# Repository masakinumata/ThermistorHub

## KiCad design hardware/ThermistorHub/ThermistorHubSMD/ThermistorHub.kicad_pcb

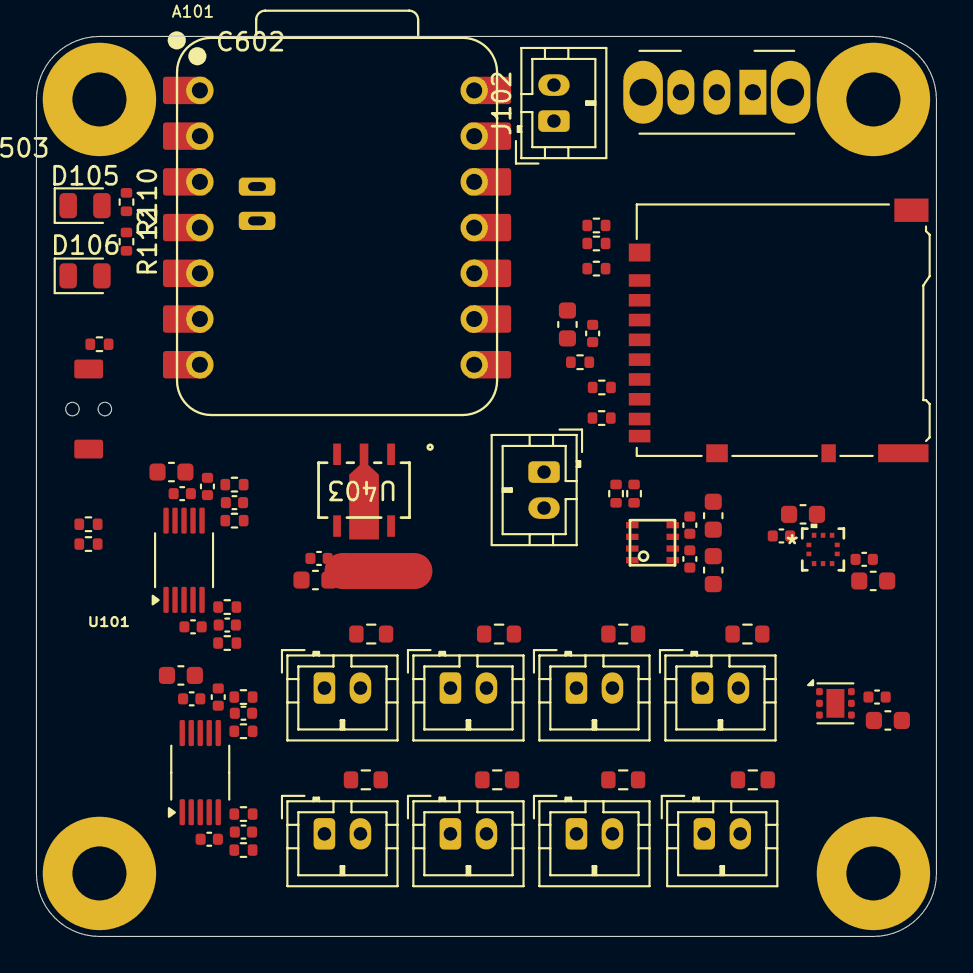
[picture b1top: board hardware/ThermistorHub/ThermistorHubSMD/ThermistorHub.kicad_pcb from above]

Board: 4 copper layers, 50.0 x 50.0 mm, 79 parts (0 on the bottom side), 40 nets, no tracks yet.

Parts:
A101: XIAO-ESP32S3-DIP
B501: Board_1U_60x60
C101, C104, C106, C107, C109, C403, C404, C406, C408: 10μF; C_0603_1608Metric
C102, C103, C105, C108, C110, C401, C402, C405, C407, C501, C502, C503, C504, C601, C602, C603, C604: 100nF; C_0402_1005Metric
D105: STAT; LED_0805_2012Metric
D106: ERROR; LED_0805_2012Metric
J101: BATPin; JST_PH_B2B-PH-K_1x02_P2.00mm_Vertical
J102: Battery; JST_PH_B2B-PH-K_1x02_P2.00mm_Vertical
J301: Micro_SD_Card_Det_Hirose_DM3AT; microSD_HC_Hirose_DM3AT-SF-PEJM5
J501: Thermistor1; JST_PH_B2B-PH-K_1x02_P2.00mm_Vertical
J502: Thermistor2; JST_PH_B2B-PH-K_1x02_P2.00mm_Vertical
J503: Thermistor3; JST_PH_B2B-PH-K_1x02_P2.00mm_Vertical
J504: Thermistor4; JST_PH_B2B-PH-K_1x02_P2.00mm_Vertical
J601: Thermistor5; JST_PH_B2B-PH-K_1x02_P2.00mm_Vertical
J602: Thermistor6; JST_PH_B2B-PH-K_1x02_P2.00mm_Vertical
J603: Thermistor7; JST_PH_B2B-PH-K_1x02_P2.00mm_Vertical
J604: Thermistor8; JST_PH_B2B-PH-K_1x02_P2.00mm_Vertical
NT401: NetTie_2; NetTie-2_SMD_Pad2.0mm
R101, R102, R103, R104, R105, R106, R107, R108, R109, R111: 10k; R_0402_1005Metric
R110, R112, R501, R503, R505, R507, R601, R603, R605, R607: 1k; R_0402_1005Metric
R303: 33Ω; R_0402_1005Metric
R502, R504, R506, R508, R602, R604, R606, R608: 47k; R_0603_1608Metric
SW101: SW_SPDT; SW_Slide_SPDT_Angled_CK_OS102011MA1Q
SW501: SW_Push; TVAF06-A020B-R
U101: BME280
U401, U402: ADS1115IRUGT; VSSOP-10_3x3mm_P0.5mm
U403: NJM2884U1-33-TE1; SOT89-5-1&slash_2_NWJ
U501: BMP390; 10LGA_2X2X0p75_BOS
U502: TMP117xxDRV; WSON-6-1EP_2x2mm_P0.65mm_EP1x1.6mm

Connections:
+3V0: C401.1, C402.1, C403.1, C404.1, C405.1, C406.1, C407.1, C408.1, J501.1, J502.1, J503.1, J504.1, J601.1, J602.1, J603.1, J604.1, R108.1, R109.1, U401.8 (VDD), U402.1 (ADDR), U402.8 (VDD), U403.4 (VOUT), U502.5 (V+)
/CLK: A101.11 (GPIO9), R303.1
/CMD: A101.10 (GPIO8), J301.3 (CMD), R103.2
/DAT0: A101.9 (GPIO7), J301.7 (DAT0), R104.2
/Thermistor/THR1: C501.2, R501.1, U401.4 (AIN0)
/Thermistor/THR2: C502.2, R503.1, U401.5 (AIN1)
/Thermistor/THR3: C503.2, R505.1, U401.6 (AIN2)
/Thermistor/THR4: C504.2, R507.1, U401.7 (AIN3)
/Thermistor/THR5: C601.2, R601.1, U402.4 (AIN0)
/Thermistor/THR6: C602.2, R603.1, U402.5 (AIN1)
/Thermistor/THR7: C603.2, R605.1, U402.6 (AIN2)
/Thermistor/THR8: C604.2, R607.1, U402.7 (AIN3)
/Thermistor/Thermisotr2/AGND: C601.1, C602.1, C603.1, C604.1, R602.2, R604.2, R606.2, R608.2
GND: A101.13 (GND), B501.GND (GND_GND), C101.2, C102.2, C103.2, C104.2, C105.2, C106.2, C107.2, C108.2, C109.2, C110.2, D105.1 (K), D106.1 (K), J301.6 (VSS), J301.10 (DET_A), J301.11 (SHIELD), NT401.2, SW501.1, U101.1 (GND), U101.5 (SDO), U101.7 (GND), U403.2 (GND), U501.3 (VSS), U501.8 (VSS), U501.9 (VSS)
GNDA: C401.2, C402.2, C403.2, C404.2, C405.2, C406.2, C407.2, C408.2, C501.1, C502.1, C503.1, C504.1, NT401.1, R502.2, R504.2, R506.2, R508.2, U401.1 (ADDR), U401.3 (GND), U402.3 (GND), U502.2 (GND)
unnamed: A101.1 (GPIO1), R110.1
unnamed: A101.2 (GPIO2), R112.1
unnamed: A101.6 (GPIO6), R111.2, SW501.2
unnamed: D105.2 (A), R110.2
unnamed: D106.2 (A), R112.2
unnamed: J101.1, J102.2
unnamed: J101.2, SW101.2 (B)
unnamed: J102.1, SW101.1 (A)
unnamed: J301.5 (CLK), R303.2
unnamed: J301.8 (DAT1), R107.2
unnamed: J301.1 (DAT2), R105.2
unnamed: J301.2 (DAT3/CD), R106.2
unnamed: J501.2, R501.2, R502.1
unnamed: J502.2, R503.2, R504.1
unnamed: J503.2, R505.2, R506.1
unnamed: J504.2, R507.2, R508.1
unnamed: J601.2, R601.2, R602.1
unnamed: J602.2, R603.2, R604.1
unnamed: J603.2, R605.2, R606.1
unnamed: J604.2, R607.2, R608.1
SCL1: A101.7 (GPIO43/TX), R102.2, U101.4 (SCK), U501.2 (SCK)
SCL2: A101.5 (GPIO5), R109.2, U401.10 (SCL), U402.10 (SCL), U502.1 (SCL)
SDA1: A101.8 (GPIO44/RX), R101.2, U101.3 (SDI), U501.4 (SDI)
SDA2: A101.4 (GPIO4), R108.2, U401.9 (SDA), U402.9 (SDA), U502.4 (ADD0), U502.6 (SDA)
VDD: A101.12 (3V3), C101.1, C102.1, C103.1, C104.1, C105.1, C106.1, C107.1, C108.1, C109.1, C110.1, J301.4 (VDD), R101.1, R102.1, R103.1, R104.1, R105.1, R106.1, R107.1, R111.1, U101.2 (CSB), U101.6 (VDDIO), U101.8 (VDD), U403.1 (CONTROL), U403.5 (VIN), U501.1 (VDDIO), U501.5 (SDO), U501.6 (CSB), U501.10 (VDD)

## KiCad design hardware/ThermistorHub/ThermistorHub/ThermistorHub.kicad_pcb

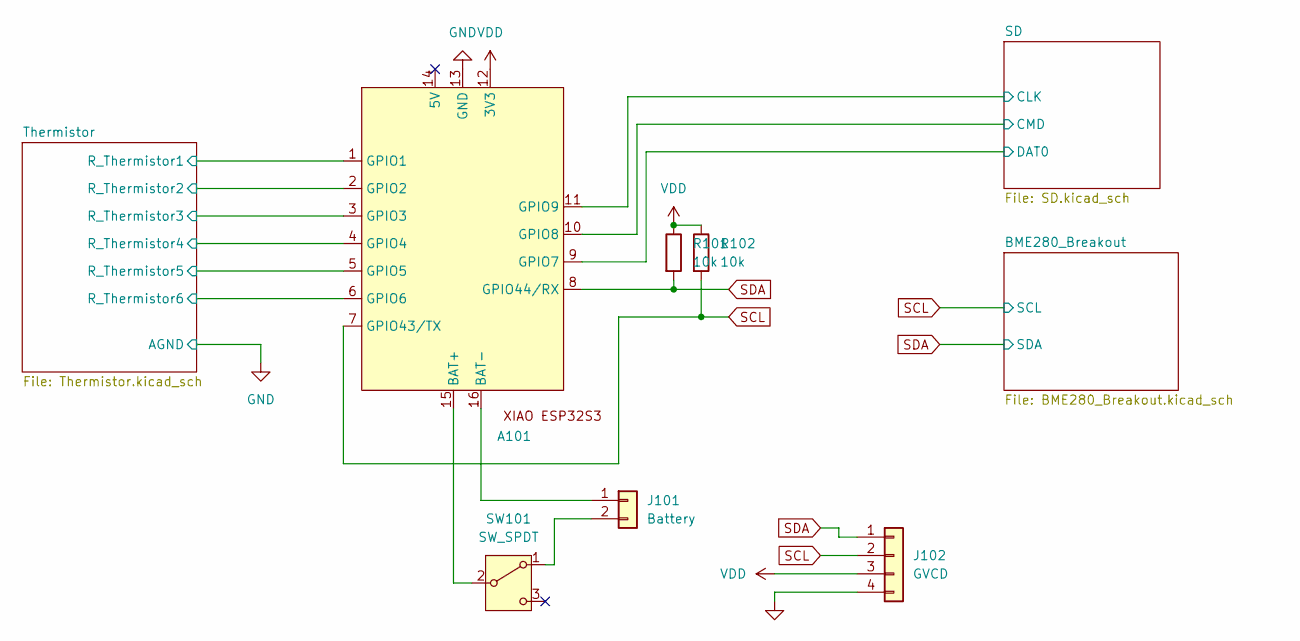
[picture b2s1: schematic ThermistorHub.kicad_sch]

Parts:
A101: XIAO-ESP32S3-DIP
J101: Battery; JST_PH_B2B-PH-K_1x02_P2.00mm_Vertical
J102: GVCD; PinHeader_1x04_P2.54mm_Vertical
R101, R102: 10k; R_Axial_DIN0204_L3.6mm_D1.6mm_P5.08mm_Horizontal
SW101: SW_SPDT; SW_Slide-03_Wuerth-WS-SLTV_10x2.5x6.4_P2.54mm

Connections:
/SD/CLK: A101.11 (GPIO9); also elsewhere on the board
/SD/CMD: A101.10 (GPIO8); also elsewhere on the board
/SD/DAT0: A101.9 (GPIO7); also elsewhere on the board
/Thermistor/R_Thermistor1: A101.1 (GPIO1); also elsewhere on the board
/Thermistor/R_Thermistor2: A101.2 (GPIO2); also elsewhere on the board
/Thermistor/R_Thermistor3: A101.3 (GPIO3); also elsewhere on the board
/Thermistor/R_Thermistor4: A101.4 (GPIO4); also elsewhere on the board
/Thermistor/R_Thermistor5: A101.5 (GPIO5); also elsewhere on the board
/Thermistor/R_Thermistor6: A101.6 (GPIO6); also elsewhere on the board
GND: A101.13 (GND), J102.4; also elsewhere on the board
unnamed 10: A101.15 (BAT+), SW101.2 (B); also elsewhere on the board
unnamed: A101.16 (BAT-), J101.1
unnamed 12: J101.2, SW101.1 (A); also elsewhere on the board
SCL: A101.7 (GPIO43/TX), J102.2, R102.2; also elsewhere on the board
SDA: A101.8 (GPIO44/RX), J102.1, R101.2; also elsewhere on the board
VDD: A101.12 (3V3), J102.3, R101.1, R102.1; also elsewhere on the board

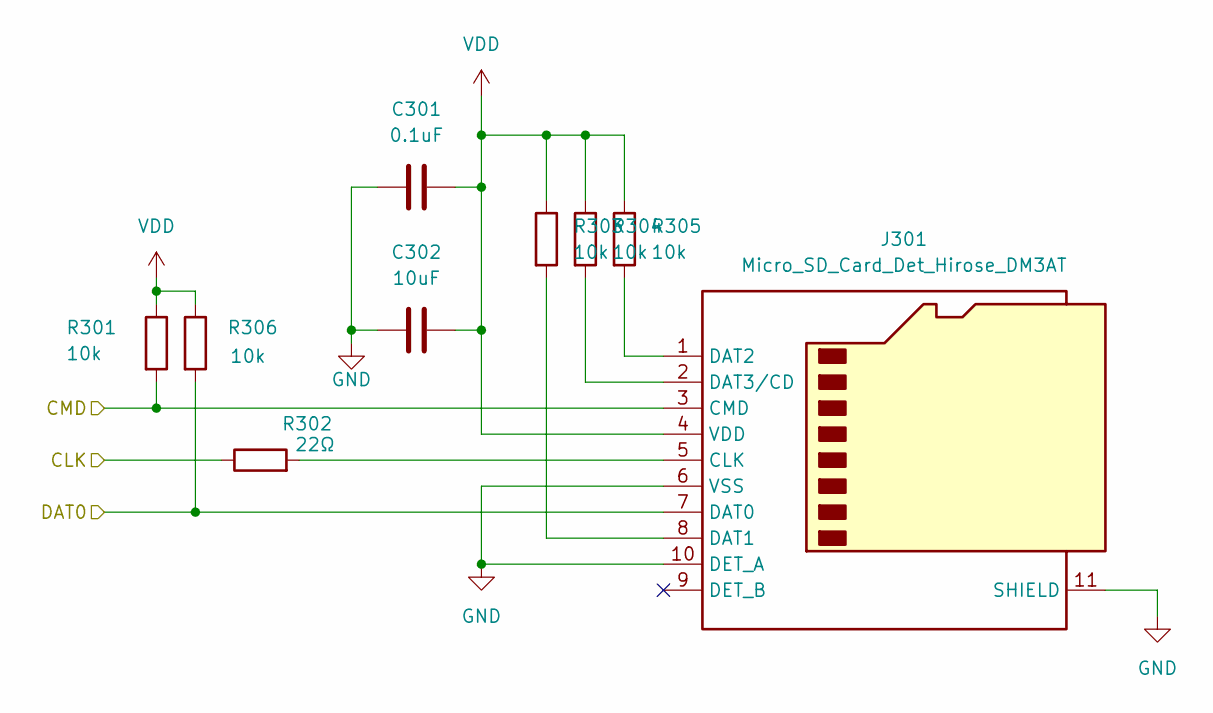
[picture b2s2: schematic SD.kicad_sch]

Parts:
C301: 0.1uF; C_Axial_L3.8mm_D2.6mm_P7.50mm_Horizontal
C302: 10uF; C_Axial_L3.8mm_D2.6mm_P7.50mm_Horizontal
J301: Micro_SD_Card_Det_Hirose_DM3AT; microSD_HC_Hirose_DM3AT-SF-PEJM5
R301, R303, R304, R305, R306: 10k; R_Axial_DIN0204_L3.6mm_D1.6mm_P5.08mm_Horizontal
R302: 22Ω; R_Axial_DIN0204_L3.6mm_D1.6mm_P5.08mm_Horizontal

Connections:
/SD/CLK: R302.1; also elsewhere on the board
/SD/CMD: J301.3 (CMD), R301.2; also elsewhere on the board
/SD/DAT0: J301.7 (DAT0), R306.2; also elsewhere on the board
GND: C301.1, C302.1, J301.6 (VSS), J301.10 (DET_A), J301.11 (SHIELD); also elsewhere on the board
unnamed: J301.5 (CLK), R302.2
unnamed: J301.8 (DAT1), R303.2
unnamed: J301.1 (DAT2), R305.2
unnamed: J301.2 (DAT3/CD), R304.2
VDD: C301.2, C302.2, J301.4 (VDD), R301.1, R303.1, R304.1, R305.1, R306.1; also elsewhere on the board

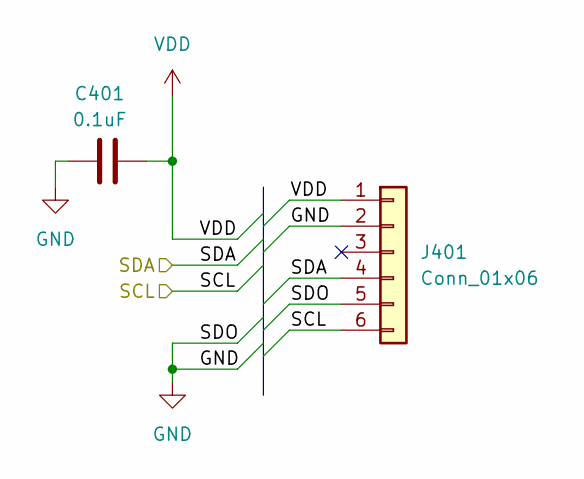
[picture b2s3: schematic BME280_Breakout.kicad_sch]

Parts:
C401: 0.1uF; C_Axial_L3.8mm_D2.6mm_P7.50mm_Horizontal
J401: Conn_01x06; PinHeader_1x06_P2.54mm_Vertical

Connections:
GND: C401.1, J401.2, J401.5; also elsewhere on the board
SCL: J401.6; also elsewhere on the board
SDA: J401.4; also elsewhere on the board
VDD: C401.2, J401.1; also elsewhere on the board

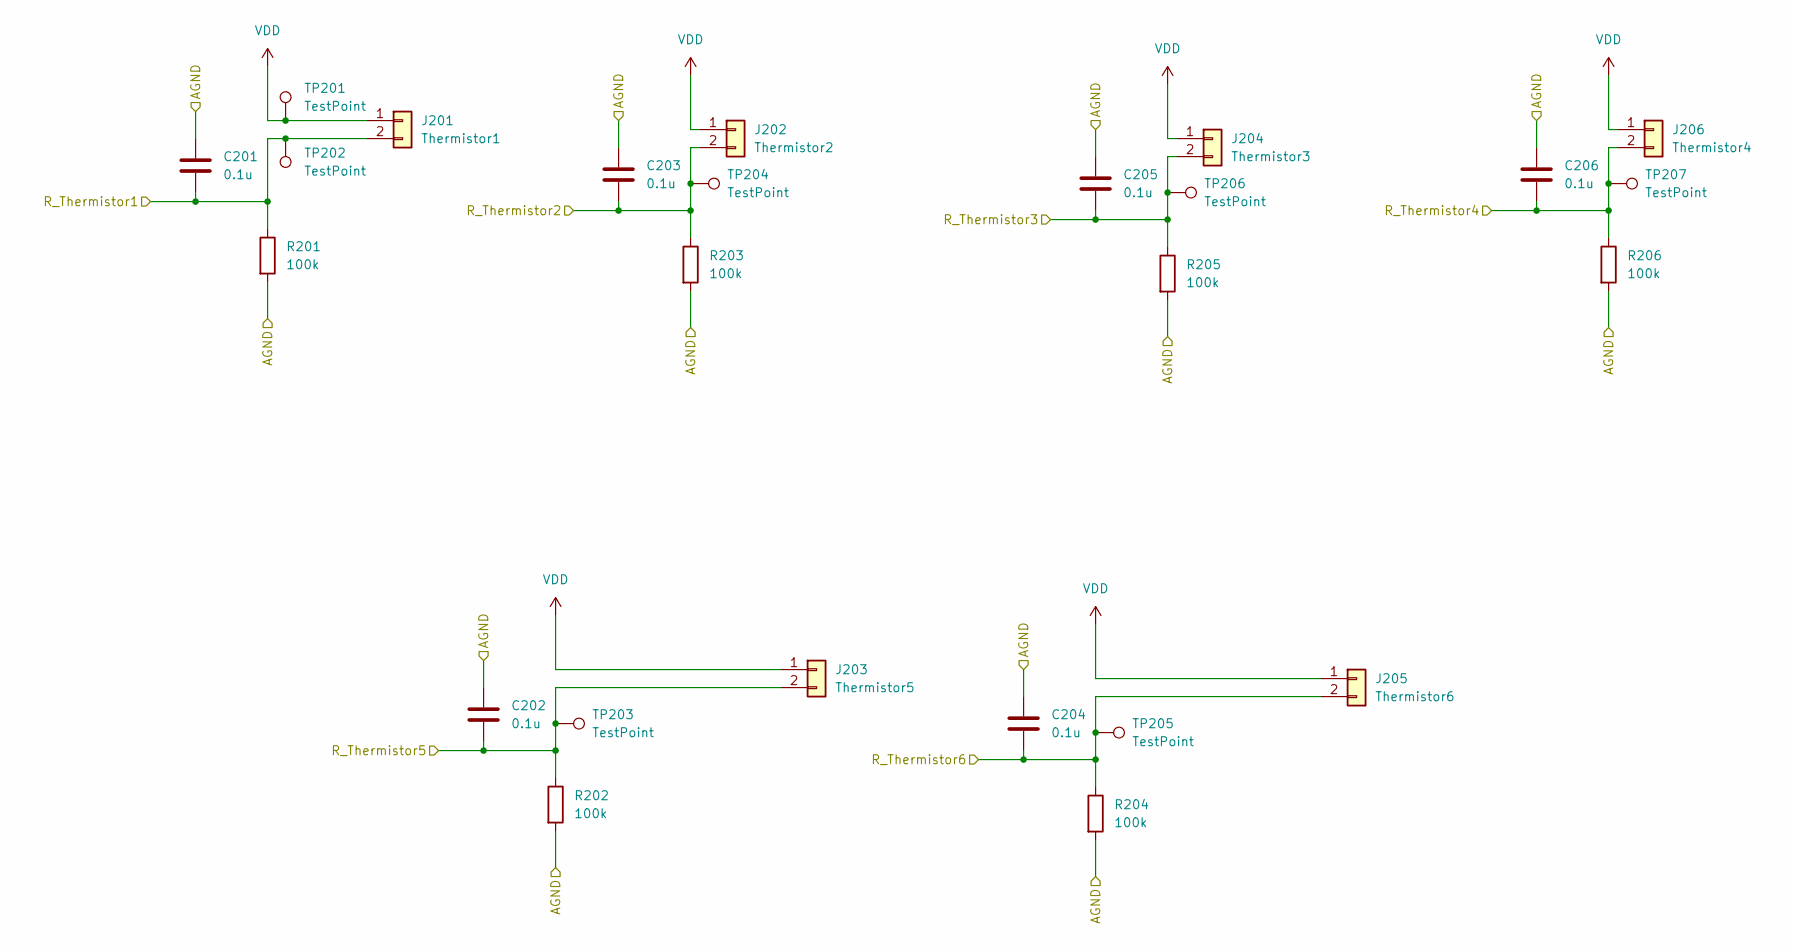
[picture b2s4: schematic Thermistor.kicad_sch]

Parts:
C201, C202, C203, C204, C205, C206: 0.1u; C_Axial_L3.8mm_D2.6mm_P7.50mm_Horizontal
J201: Thermistor1; JST_PH_B2B-PH-K_1x02_P2.00mm_Vertical
J202: Thermistor2; JST_PH_B2B-PH-K_1x02_P2.00mm_Vertical
J203: Thermistor5; JST_PH_B2B-PH-K_1x02_P2.00mm_Vertical
J204: Thermistor3; JST_PH_B2B-PH-K_1x02_P2.00mm_Vertical
J205: Thermistor6; JST_PH_B2B-PH-K_1x02_P2.00mm_Vertical
J206: Thermistor4; JST_PH_B2B-PH-K_1x02_P2.00mm_Vertical
R201, R202, R203, R204, R205, R206: 100k; R_Axial_DIN0204_L3.6mm_D1.6mm_P5.08mm_Horizontal
TP201, TP202, TP203, TP204, TP205, TP206, TP207: TestPoint; PinHeader_1x01_P2.54mm_Vertical

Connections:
/Thermistor/R_Thermistor1: C201.2, J201.2, R201.1, TP202.1; also elsewhere on the board
/Thermistor/R_Thermistor2: C203.2, J202.2, R203.1, TP204.1; also elsewhere on the board
/Thermistor/R_Thermistor3: C205.2, J204.2, R205.1, TP206.1; also elsewhere on the board
/Thermistor/R_Thermistor4: C206.2, J206.2, R206.1, TP207.1; also elsewhere on the board
/Thermistor/R_Thermistor5: C202.2, J203.2, R202.1, TP203.1; also elsewhere on the board
/Thermistor/R_Thermistor6: C204.2, J205.2, R204.1, TP205.1; also elsewhere on the board
GND: C201.1, C202.1, C203.1, C204.1, C205.1, C206.1, R201.2, R202.2, R203.2, R204.2, R205.2, R206.2; also elsewhere on the board
VDD: J201.1, J202.1, J203.1, J204.1, J205.1, J206.1, TP201.1; also elsewhere on the board

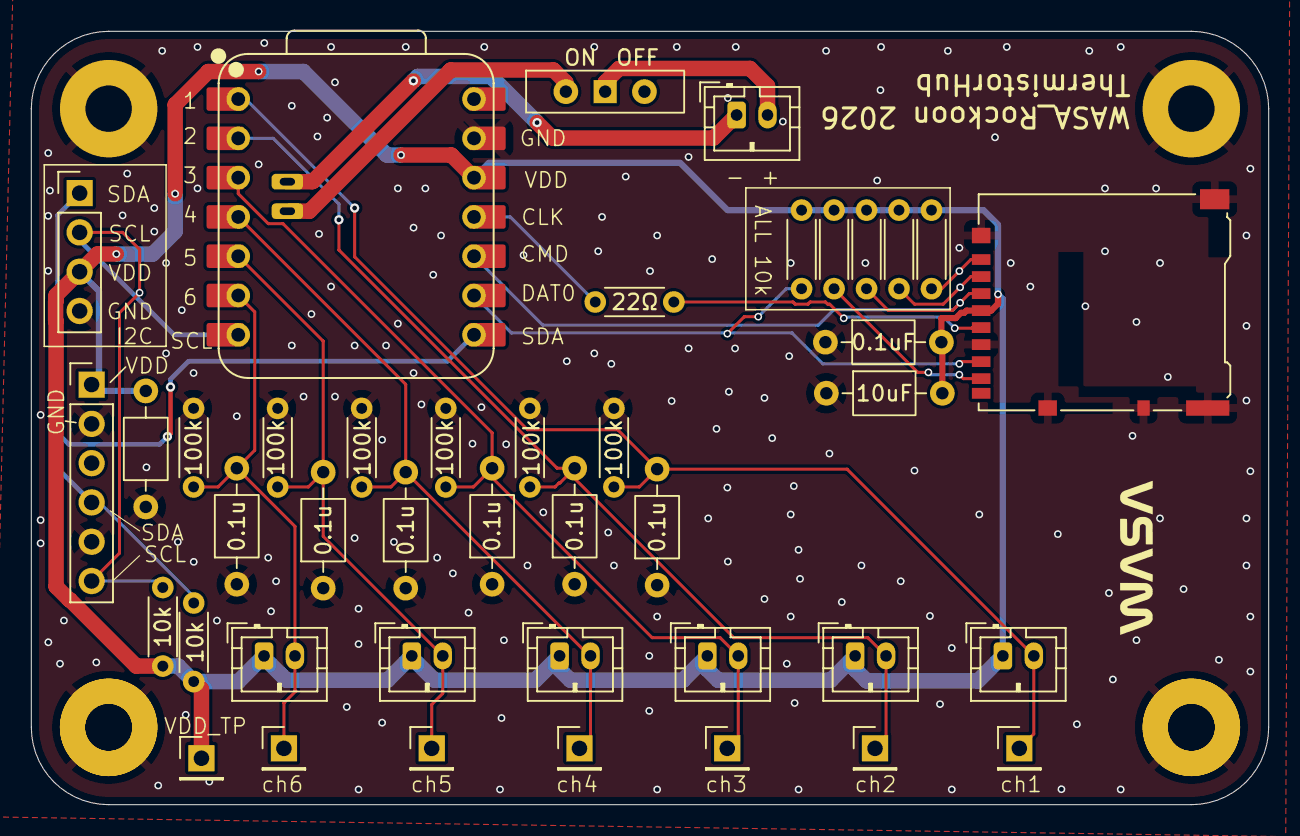
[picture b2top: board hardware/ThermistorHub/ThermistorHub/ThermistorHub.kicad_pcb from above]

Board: 2 copper layers, 80.0 x 50.0 mm, 42 parts (0 on the bottom side), 20 nets.

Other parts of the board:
ON: SW_SPDT; SW_Slide-03_Wuerth-WS-SLTV_10x2.5x6.4_P2.54mm

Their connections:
unnamed 10: ON.2 (B); also elsewhere on the board
unnamed 12: ON.1 (A); also elsewhere on the board

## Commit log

2026-02-01 Fix typo in project name from 'Thermister' to 'Thermistor'
2026-02-01 Kicad
2026-02-22 src追加
2026-02-25 CHに名前つけた
2026-04-05 SMD版を製作中
2026-04-06 途中まで
